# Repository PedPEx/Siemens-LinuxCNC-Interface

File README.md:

# Siemens Sinumerik840C control panel Interface (WIP! - UNTESTED!)
This interface board is designed to be placed on the backside of an [old type](https://mall.industry.siemens.com/mall/de/de/Catalog/Product/6FC5103-0AD03-0AA0) Siemens Sinumerik840C machine control panel in order to be used as user input in LinuxCNC. I reverse engineered a control panel of type M (CNC-Mill - 6FC5103-0AD03-0AA0) for this project. All the IOs of these control panels are accessible through the two 64pin pinheaders. You can get these machine control panels pretty cheap on ebay.

Interface:

Sinumerik840C Machine Control Panel:

## ToDo
- ✅ finished prototype PCB (v0.9.5)
- 🔲 finished prototype PCB (v0.9.6)
- ✅ firmware for STM32L151CC (technically 100% - needs cleanup and timeout detection on LinuxCNC side)
- 🔲 tested intensively with LinuxCNC
- 🔲 example config for LinuxCNC

## Powering
The board needs no seperate supply voltage and is fully powered by the USB Interface. A power distribution switch deactivates the whole interface in case of an overcurrent (set to 1.0 A).

## USB port
Plug in a USB-C cable and use the provided strain relief with the help of a 5mm cable tie. With this USB connection a virtual serial port is used to send the data to the host. More information in the [software](#usagesoftware) details.

## Terminal blocks and general IO
Most of the IO on the three terminal blocks is directly wired into the microcontroller. They can be used for analog inputs or for further expansion in general.

As terminal blocks [Weidmüller 1824460000 - LSF-SMT 3.50/06/90 3.5SN BK TU](https://catalog.weidmueller.com/catalog/Start.do?ObjectID=1824460000) were used - because i had them at hand. But any headers or screw terminals with a 3.5 mm pitch can be used here.

## Usage/Software
This interface board is meant to be used in combination with the software [LinuxCNC_ArduinoConnector](https://github.com/AlexmagToast/LinuxCNC_ArduinoConnector). It does not operate with an Arduino, but with a much more capable [STM32L151C8](https://www.st.com/en/microcontrollers-microprocessors/stm32l151cc.html). The STM32 just emulates a serial port and sends the same signals to the LinuxCNC component like the Arduino would. The L1 series of STM32 was chosen because of its bootloader

## Limitations
Do not use this board for any time critical porpuses!

## Online Preview / BOM
[Detailed schematics preview](https://kicanvas.org/?github=https%3A%2F%2Fgithub.com%2FPedPEx%2FSiemens-LinuxCNC-Interface%2Ftree%2Fmaster%2F1_hardware) (KiCanvas)

[Online BOM](https://htmlpreview.github.io/?https://raw.githubusercontent.com/PedPEx/Siemens-LinuxCNC-Interface/master/1_hardware/bom/webviewer-BOM.html)

[3D Preview](https://github.com/PedPEx/Siemens-LinuxCNC-Interface/blob/master/1_hardware/Siemens-Sinumerik840C-Maschinensteuertafel-Adaptor.stl)

## LinuxCNC config (TODO)
When finished, an example config for LinuxCNC can be found in the [correspondig folder](https://github.com/PedPEx/Siemens-LinuxCNC-Interface/tree/master/2_software_LinuxCNC).

An example of a whole machine fitted with this Interface can be found in my other project [Maho400E-LinuxCNC](https://github.com/PedPEx/Maho400E-LinuxCNC)

## *Note*
The pictures were rendered with the help of Blender and the [pcb2blender](https://github.com/30350n/pcb2blender) plugin and the HTML BOM was created with [InteractiveHtmlBom](https://github.com/openscopeproject/InteractiveHtmlBom).

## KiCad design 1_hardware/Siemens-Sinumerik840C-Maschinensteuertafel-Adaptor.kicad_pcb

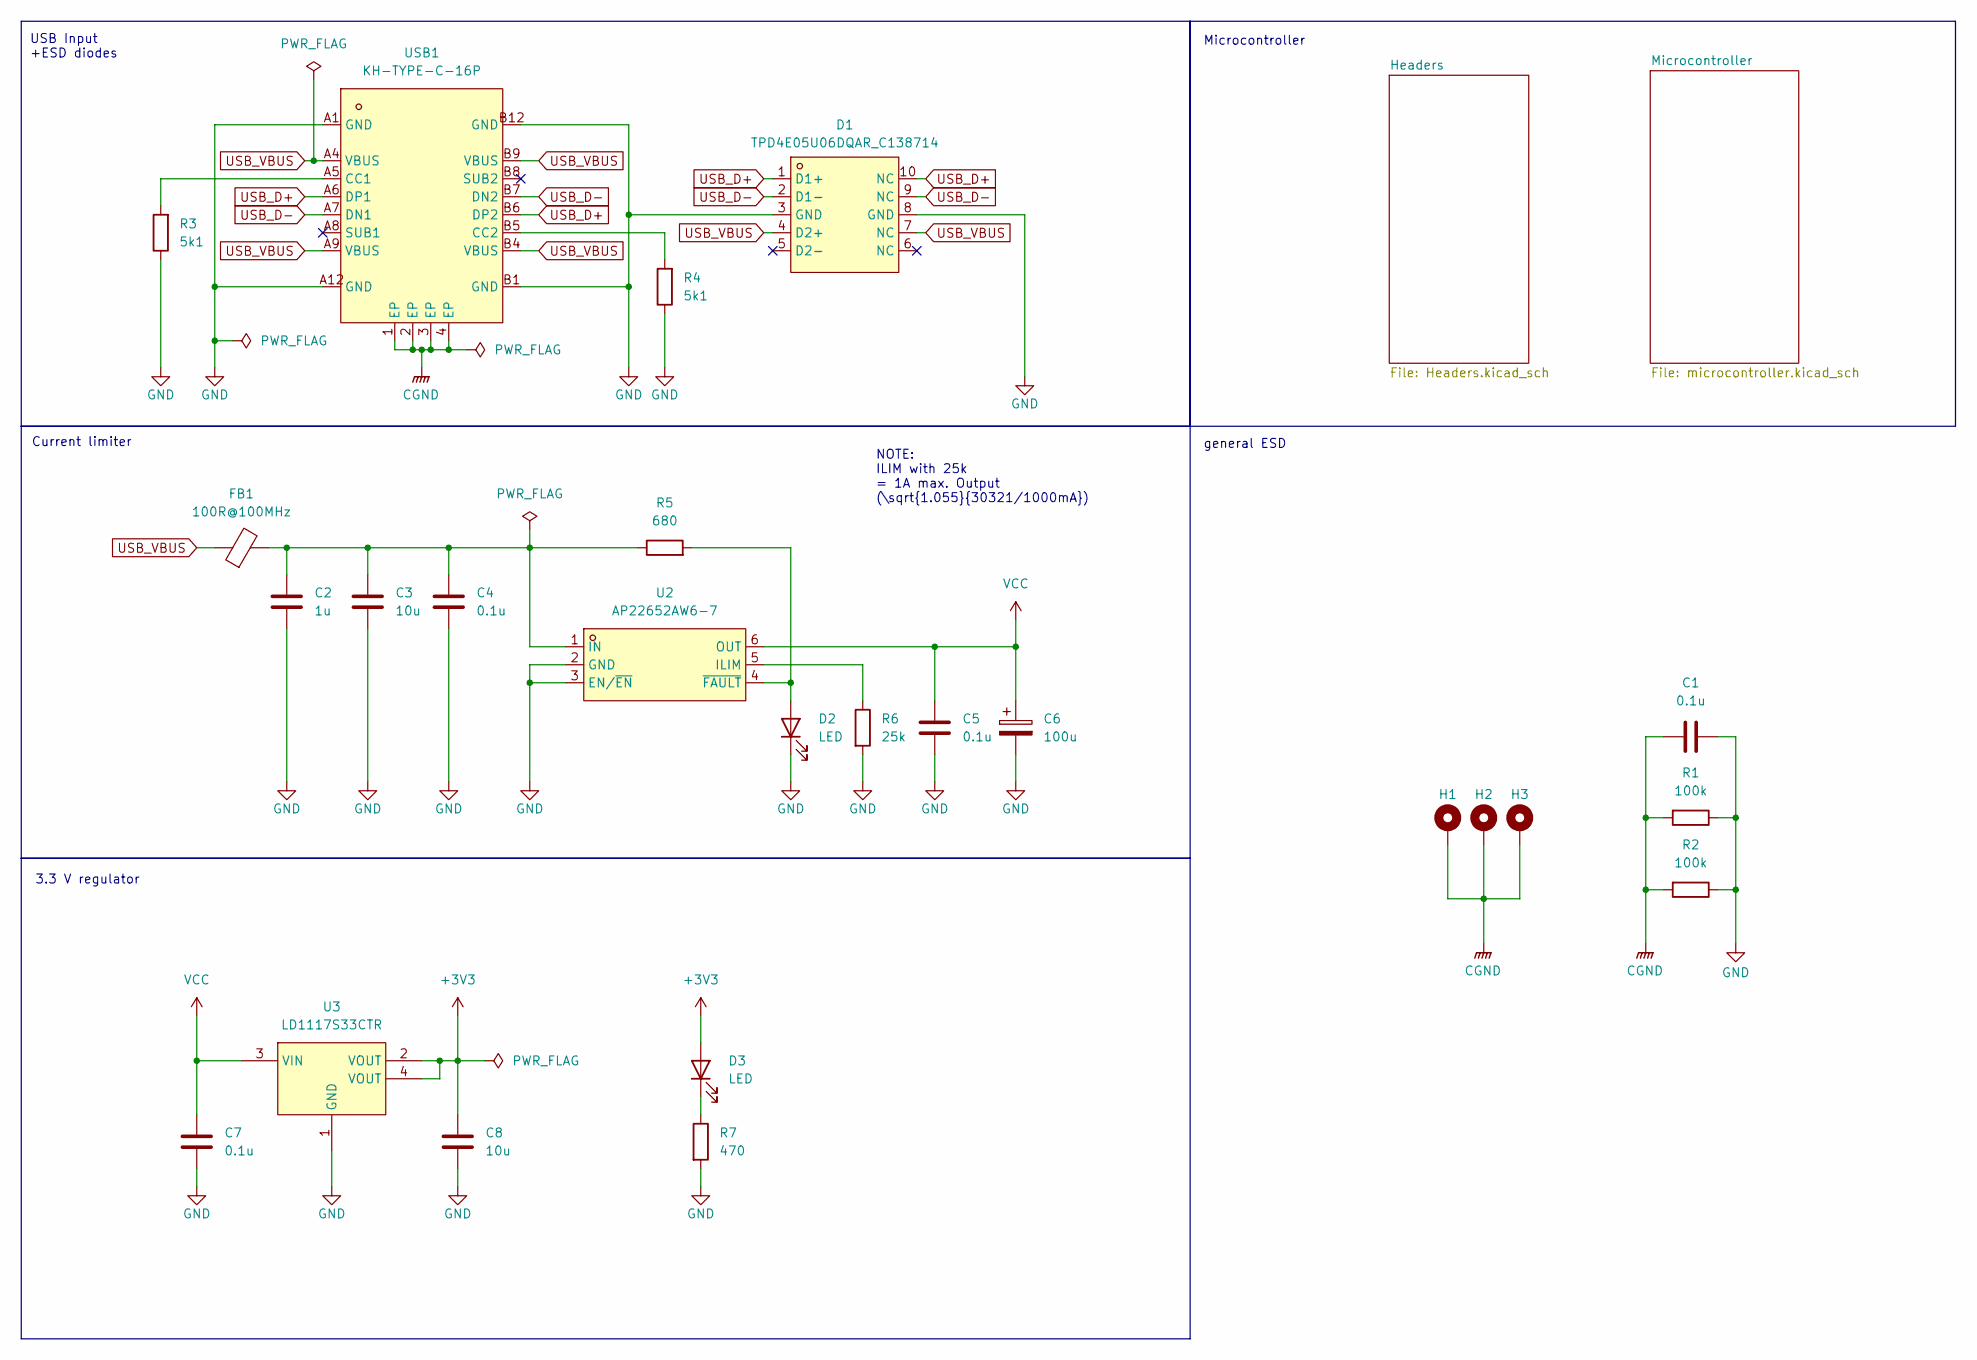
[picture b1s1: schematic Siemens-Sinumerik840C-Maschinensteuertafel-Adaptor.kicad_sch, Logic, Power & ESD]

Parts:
C1: 0.1u; C_2220_5750Metric; LCSC Part C5290327
C2: 1u; C_0603_1608Metric
C3, C8: 10u; C_0603_1608Metric
C4, C5, C7: 0.1u; C_0603_1608Metric
C6: 100u; CP_Elec_5x5.8; LCSC Part C336771
D1: TPD4E05U06DQAR_C138714; USON-10_L2.5-W1.0-P0.50-BL; LCSC Part C138714
D2, D3: LED; LED_0603_1608Metric
FB1: 100R@100MHz; L0603; LCSC Part C107332
H1, H2, H3: MountingHole_Pad_MP; MountingHole_3.2mm_M3_DIN965_Pad
R1, R2: 100k; R_2512_6332Metric; LCSC Part C25717
R3, R4: 5k1; R_0603_1608Metric
R5: 680; R_0603_1608Metric
R6: 25k; R_0603_1608Metric
R7: 470; R_0603_1608Metric
U2: AP22652AW6-7; SOT-23-6_L2.9-W1.6-P0.95-LS2.8-BL; LCSC Part C5329413
U3: LD1117S33CTR; SOT-223-4_L6.5-W3.5-P2.30-LS7.0-BR; LCSC Part C35879
USB1: KH-TYPE-C-16P; USB-C-SMD_KH-TYPE-C-16P; LCSC Part C709357

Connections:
+3V3: C8.2, D3.2 (A), U3.2 (VOUT), U3.4 (VOUT); also elsewhere on the board
CGND: C1.2, H1.1, H2.1, H3.1, R1.2, R2.2, USB1.1 (EP), USB1.2 (EP), USB1.3 (EP), USB1.4 (EP)
GND: C1.1, C2.1, C3.1, C4.1, C5.1, C6.2, C7.1, C8.1, D1.3 (GND), D1.8 (GND), D2.1 (K), R1.1, R2.1, R3.1, R4.1, R6.2, R7.2, U2.2 (GND), U2.3 (EN/~EN), U3.1 (GND), USB1.A1 (GND), USB1.A12 (GND), USB1.B1 (GND), USB1.B12 (GND); also elsewhere on the board
unnamed: D2.2 (A), R5.2, U2.4 (~FAULT)
unnamed: D3.1 (K), R7.1
unnamed: R6.1, U2.5 (ILIM)
unnamed: C2.2, C3.2, C4.2, FB1.2, R5.1, U2.1 (IN)
unnamed: R3.2, USB1.A5 (CC1)
unnamed: R4.2, USB1.B5 (CC2)
USB_D+: D1.1 (D1+), D1.10 (NC), USB1.A6 (DP1), USB1.B6 (DP2); also elsewhere on the board
USB_D-: D1.2 (D1-), D1.9 (NC), USB1.A7 (DN1), USB1.B7 (DN2); also elsewhere on the board
USB_VBUS: D1.4 (D2+), D1.7 (NC), FB1.1, USB1.A4 (VBUS), USB1.A9 (VBUS), USB1.B4 (VBUS), USB1.B9 (VBUS)
VCC: C5.2, C6.1, C7.2, U2.6 (OUT), U3.3 (VIN); also elsewhere on the board

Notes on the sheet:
3.3 V regulator
NOTE: ILIM with 25k = 1A max. Output (\sqrt{1.055}{30321/1000mA})
Microcontroller
Current limiter
general ESD
USB Input +ESD diodes

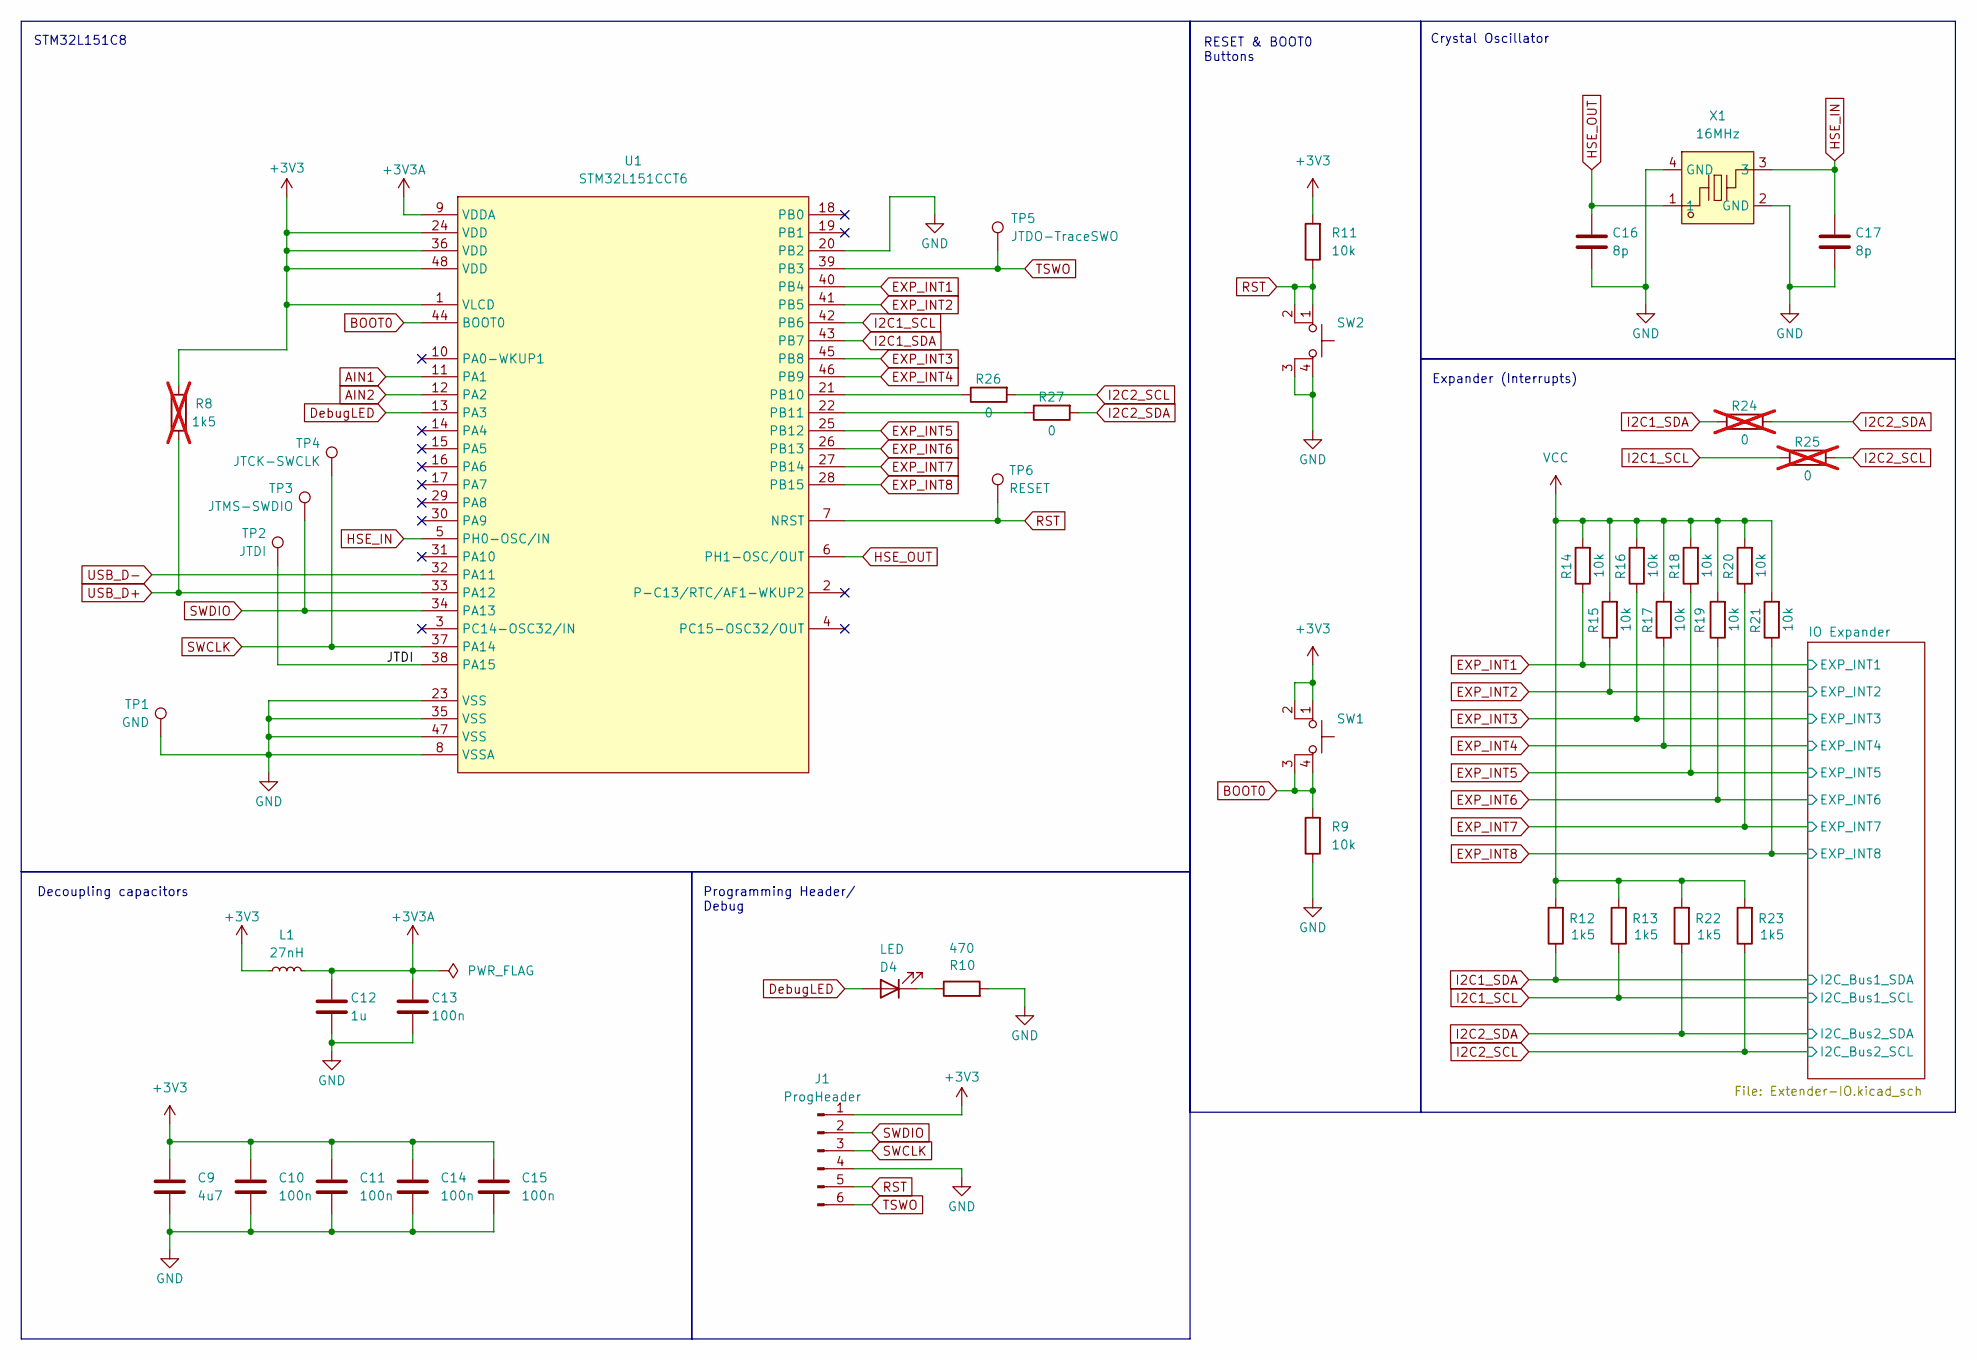
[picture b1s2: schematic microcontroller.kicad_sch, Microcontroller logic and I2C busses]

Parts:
C9: 4u7; C_0603_1608Metric
C10, C11, C13, C14, C15: 100n; C_0603_1608Metric
C12: 1u; C_0603_1608Metric
C16, C17: 8p; C_0603_1608Metric
D4: LED; LED_0603_1608Metric
J1: ProgHeader; HDR-SMD_6P-P2.54-V-M-LS4.8_R2; LCSC Part C2883763
L1: 27nH; L_0603_1608Metric; LCSC Part C12100
R8: 1k5; R_0603_1608Metric; not fitted
R9, R11, R14, R15, R16, R17, R18, R19, R20, R21: 10k; R_0603_1608Metric
R10: 470; R_0603_1608Metric
R12, R13, R22, R23: 1k5; R_0603_1608Metric
R24, R25: 0; R_0603_1608Metric; not fitted
R26, R27: 0; R_0603_1608Metric
SW1, SW2: TS-1187A-B-A-B; SW-SMD_4P-L5.1-W5.1-P3.70-LS6.5-TL-2; LCSC Part C318884
TP1: GND; TestPoint_Pad_D1.0mm
TP2: JTDI; TestPoint_Pad_D1.0mm
TP3: JTMS-SWDIO; TestPoint_Pad_D1.0mm
TP4: JTCK-SWCLK; TestPoint_Pad_D1.0mm
TP5: JTDO-TraceSWO; TestPoint_Pad_D1.0mm
TP6: RESET; TestPoint_Pad_D1.0mm
U1: STM32L151CCT6; LQFP-48_L7.0-W7.0-P0.50-LS9.0-BL; LCSC Part C2149675
X1: 16MHz; CRYSTAL-SMD_4P-L3.2-W2.5-BL_SIT8008BI; LCSC Part C498200

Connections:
+3V3: C9.2, C10.2, C11.2, C14.2, C15.2, J1.1, L1.1, R8.1, R11.2, SW1.1, SW1.2, U1.1 (VLCD), U1.24 (VDD), U1.36 (VDD), U1.48 (VDD); also elsewhere on the board
+3V3A: C12.2, C13.2, L1.2, U1.9 (VDDA)
/Microcontroller/JTDI: TP2.1, U1.38 (PA15)
AIN1: U1.11 (PA1); also elsewhere on the board
AIN2: U1.12 (PA2); also elsewhere on the board
BOOT0: R9.2, SW1.3 (K), SW1.4 (A), U1.44 (BOOT0)
DebugLED: D4.2 (A), U1.13 (PA3)
EXP_INT1: R14.1, U1.40 (PB4); also elsewhere on the board
EXP_INT2: R15.1, U1.41 (PB5); also elsewhere on the board
EXP_INT3: R16.1, U1.45 (PB8); also elsewhere on the board
EXP_INT4: R17.1, U1.46 (PB9); also elsewhere on the board
EXP_INT5: R18.1, U1.25 (PB12); also elsewhere on the board
EXP_INT6: R19.1, U1.26 (PB13); also elsewhere on the board
EXP_INT7: R20.1, U1.27 (PB14); also elsewhere on the board
EXP_INT8: R21.1, U1.28 (PB15); also elsewhere on the board
GND: C9.1, C10.1, C11.1, C12.1, C13.1, C14.1, C15.1, C16.1, C17.1, J1.4, R9.1, R10.2, SW2.3 (K), SW2.4 (A), TP1.1, U1.8 (VSSA), U1.20 (PB2), U1.23 (VSS), U1.35 (VSS), U1.47 (VSS), X1.2 (GND), X1.4 (GND); also elsewhere on the board
HSE_IN: C17.2, U1.5 (PH0-OSC/IN), X1.3
HSE_OUT: C16.2, U1.6 (PH1-OSC/OUT), X1.1
I2C1_SCL: R13.1, R25.1, U1.42 (PB6); also elsewhere on the board
I2C1_SDA: R12.1, R24.1, U1.43 (PB7); also elsewhere on the board
I2C2_SCL: R23.1, R25.2, R26.2; also elsewhere on the board
I2C2_SDA: R22.1, R24.2, R27.2; also elsewhere on the board
unnamed: D4.1 (K), R10.1
unnamed: R26.1, U1.21 (PB10)
unnamed: R27.1, U1.22 (PB11)
RST: J1.5, R11.1, SW2.1, SW2.2, TP6.1, U1.7 (NRST)
SWCLK: J1.3, TP4.1, U1.37 (PA14)
SWDIO: J1.2, TP3.1, U1.34 (PA13)
TSWO: J1.6, TP5.1, U1.39 (PB3)
USB_D+: R8.2, U1.33 (PA12); also elsewhere on the board
USB_D-: U1.32 (PA11); also elsewhere on the board
VCC: R12.2, R13.2, R14.2, R15.2, R16.2, R17.2, R18.2, R19.2, R20.2, R21.2, R22.2, R23.2; also elsewhere on the board

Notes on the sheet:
STM32L151C8
RESET & BOOT0 Buttons
Crystal Oscillator
Decoupling capacitors
Programming Header/ Debug
Expander (Interrupts)

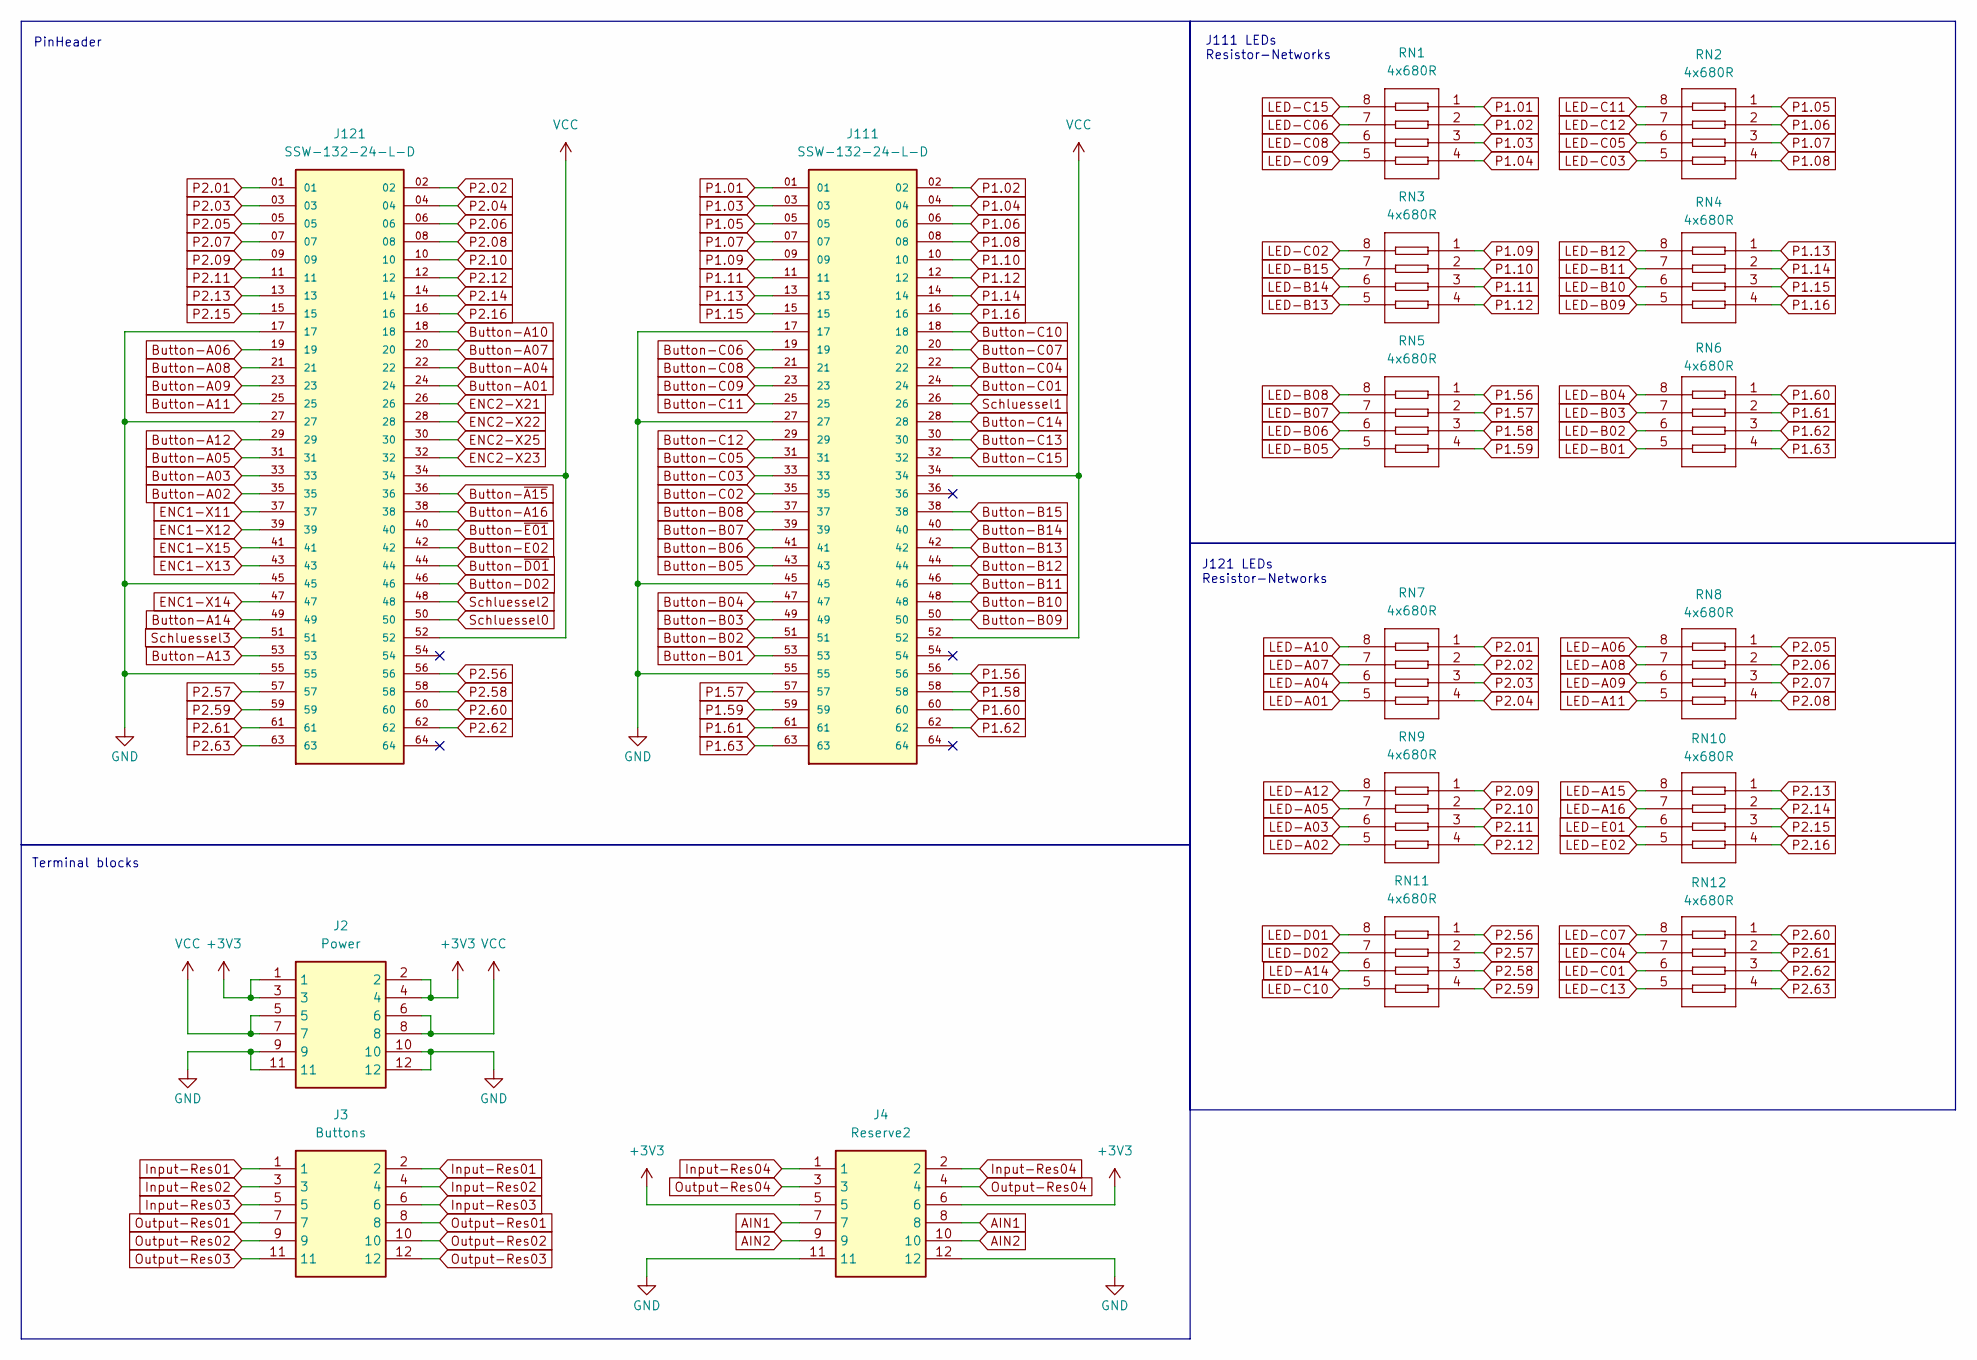
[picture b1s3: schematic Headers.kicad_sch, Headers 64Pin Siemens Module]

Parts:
J2: Power; 1824460000 - LSF-SMT 3.500690 3.5SN BK TU; Manufacturer_Part_Number 1824460000; Mouser Part Number 470-1824460000
J3: Buttons; 1824460000 - LSF-SMT 3.500690 3.5SN BK TU; Manufacturer_Part_Number 1824460000; Mouser Part Number 470-1824460000
J4: Reserve2; 1824460000 - LSF-SMT 3.500690 3.5SN BK TU; Manufacturer_Part_Number 1824460000; Mouser Part Number 470-1824460000
J111, J121: SSW-132-24-L-D; SAMTEC_SSW-132-24-L-D; PARTREV R
RN1, RN2, RN3, RN4, RN5, RN6, RN7, RN8, RN9, RN10, RN11, RN12: 4x680R; RES-ARRAY-SMD_0603-8P-L3.2-W1.6-BL; LCSC Part C12035

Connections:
+3V3: J2.1, J2.2, J2.3, J2.4, J4.5, J4.6; also elsewhere on the board
AIN1: J4.7, J4.8; also elsewhere on the board
AIN2: J4.9, J4.10; also elsewhere on the board
Button-A01: J121.24; also elsewhere on the board
Button-A02: J121.35; also elsewhere on the board
Button-A03: J121.33; also elsewhere on the board
Button-A04: J121.22; also elsewhere on the board
Button-A05: J121.31; also elsewhere on the board
Button-A06: J121.19; also elsewhere on the board
Button-A07: J121.20; also elsewhere on the board
Button-A08: J121.21; also elsewhere on the board
Button-A09: J121.23; also elsewhere on the board
Button-A10: J121.18; also elsewhere on the board
Button-A11: J121.25; also elsewhere on the board
Button-A12: J121.29; also elsewhere on the board
Button-A13: J121.53; also elsewhere on the board
Button-A14: J121.49; also elsewhere on the board
Button-A16: J121.38; also elsewhere on the board
Button-B01: J111.53; also elsewhere on the board
Button-B02: J111.51; also elsewhere on the board
Button-B03: J111.49; also elsewhere on the board
Button-B04: J111.47; also elsewhere on the board
Button-B05: J111.43; also elsewhere on the board
Button-B06: J111.41; also elsewhere on the board
Button-B07: J111.39; also elsewhere on the board
Button-B08: J111.37; also elsewhere on the board
Button-B09: J111.50; also elsewhere on the board
Button-B10: J111.48; also elsewhere on the board
Button-B11: J111.46; also elsewhere on the board
Button-B12: J111.44; also elsewhere on the board
Button-B13: J111.42; also elsewhere on the board
Button-B14: J111.40; also elsewhere on the board
Button-B15: J111.38; also elsewhere on the board
Button-C01: J111.24; also elsewhere on the board
Button-C02: J111.35; also elsewhere on the board
Button-C03: J111.33; also elsewhere on the board
Button-C04: J111.22; also elsewhere on the board
Button-C05: J111.31; also elsewhere on the board
Button-C06: J111.19; also elsewhere on the board
Button-C07: J111.20; also elsewhere on the board
Button-C08: J111.21; also elsewhere on the board
Button-C09: J111.23; also elsewhere on the board
Button-C10: J111.18; also elsewhere on the board
Button-C11: J111.25; also elsewhere on the board
Button-C12: J111.29; also elsewhere on the board
Button-C13: J111.30; also elsewhere on the board
Button-C14: J111.28; also elsewhere on the board
Button-C15: J111.32; also elsewhere on the board
Button-D02: J121.46; also elsewhere on the board
Button-E02: J121.42; also elsewhere on the board
Button-~A15: J121.36; also elsewhere on the board
Button-~D01: J121.44; also elsewhere on the board
Button-~E01: J121.40; also elsewhere on the board
ENC1-X11: J121.37; also elsewhere on the board
ENC1-X12: J121.39; also elsewhere on the board
ENC1-X13: J121.43; also elsewhere on the board
ENC1-X14: J121.47; also elsewhere on the board
ENC1-X15: J121.41; also elsewhere on the board
ENC2-X21: J121.26; also elsewhere on the board
ENC2-X22: J121.28; also elsewhere on the board
ENC2-X23: J121.32; also elsewhere on the board
ENC2-X25: J121.30; also elsewhere on the board
GND: J2.9, J2.10, J2.11, J2.12, J4.11, J4.12, J111.17, J111.27, J111.45, J111.55, J121.17, J121.27, J121.45, J121.55; also elsewhere on the board
Input-Res01: J3.1, J3.2; also elsewhere on the board
Input-Res02: J3.3, J3.4; also elsewhere on the board
Input-Res03: J3.5, J3.6; also elsewhere on the board
Input-Res04: J4.1, J4.2; also elsewhere on the board
LED-A01: RN7.5; also elsewhere on the board
LED-A02: RN9.5; also elsewhere on the board
LED-A03: RN9.6; also elsewhere on the board
LED-A04: RN7.6; also elsewhere on the board
LED-A05: RN9.7; also elsewhere on the board
LED-A06: RN8.8; also elsewhere on the board
LED-A07: RN7.7; also elsewhere on the board
LED-A08: RN8.7; also elsewhere on the board
LED-A09: RN8.6; also elsewhere on the board
LED-A10: RN7.8; also elsewhere on the board
LED-A11: RN8.5; also elsewhere on the board
LED-A12: RN9.8; also elsewhere on the board
LED-A14: RN11.6; also elsewhere on the board
LED-A15: RN10.8; also elsewhere on the board
LED-A16: RN10.7; also elsewhere on the board
LED-B01: RN6.5; also elsewhere on the board
LED-B02: RN6.6; also elsewhere on the board
LED-B03: RN6.7; also elsewhere on the board
LED-B04: RN6.8; also elsewhere on the board
LED-B05: RN5.5; also elsewhere on the board
LED-B06: RN5.6; also elsewhere on the board
LED-B07: RN5.7; also elsewhere on the board
LED-B08: RN5.8; also elsewhere on the board
LED-B09: RN4.5; also elsewhere on the board
LED-B10: RN4.6; also elsewhere on the board
LED-B11: RN4.7; also elsewhere on the board
LED-B12: RN4.8; also elsewhere on the board
LED-B13: RN3.5; also elsewhere on the board
LED-B14: RN3.6; also elsewhere on the board
LED-B15: RN3.7; also elsewhere on the board
LED-C01: RN12.6; also elsewhere on the board
LED-C02: RN3.8; also elsewhere on the board
LED-C03: RN2.5; also elsewhere on the board
LED-C04: RN12.7; also elsewhere on the board
LED-C05: RN2.6; also elsewhere on the board
LED-C06: RN1.7; also elsewhere on the board
LED-C07: RN12.8; also elsewhere on the board
LED-C08: RN1.6; also elsewhere on the board
LED-C09: RN1.5; also elsewhere on the board
LED-C10: RN11.5; also elsewhere on the board
LED-C11: RN2.8; also elsewhere on the board
LED-C12: RN2.7; also elsewhere on the board
LED-C13: RN12.5; also elsewhere on the board
LED-C15: RN1.8; also elsewhere on the board
LED-D01: RN11.8; also elsewhere on the board
LED-D02: RN11.7; also elsewhere on the board
LED-E01: RN10.6; also elsewhere on the board
LED-E02: RN10.5; also elsewhere on the board
Output-Res01: J3.7, J3.8; also elsewhere on the board
Output-Res02: J3.9, J3.10; also elsewhere on the board
Output-Res03: J3.11, J3.12; also elsewhere on the board
Output-Res04: J4.3, J4.4; also elsewhere on the board
P1.01: J111.01, RN1.1
P1.02: J111.02, RN1.2
P1.03: J111.03, RN1.3
P1.04: J111.04, RN1.4
P1.05: J111.05, RN2.1
P1.06: J111.06, RN2.2
P1.07: J111.07, RN2.3
P1.08: J111.08, RN2.4
P1.09: J111.09, RN3.1
P1.10: J111.10, RN3.2
P1.11: J111.11, RN3.3
P1.12: J111.12, RN3.4
P1.13: J111.13, RN4.1
P1.14: J111.14, RN4.2
P1.15: J111.15, RN4.3
P1.16: J111.16, RN4.4
P1.56: J111.56, RN5.1
P1.57: J111.57, RN5.2
P1.58: J111.58, RN5.3
P1.59: J111.59, RN5.4
P1.60: J111.60, RN6.1
P1.61: J111.61, RN6.2
P1.62: J111.62, RN6.3
P1.63: J111.63, RN6.4
P2.01: J121.01, RN7.1
P2.02: J121.02, RN7.2
P2.03: J121.03, RN7.3
P2.04: J121.04, RN7.4
P2.05: J121.05, RN8.1
P2.06: J121.06, RN8.2
P2.07: J121.07, RN8.3
P2.08: J121.08, RN8.4
P2.09: J121.09, RN9.1
P2.10: J121.10, RN9.2
P2.11: J121.11, RN9.3
P2.12: J121.12, RN9.4
P2.13: J121.13, RN10.1
P2.14: J121.14, RN10.2
P2.15: J121.15, RN10.3
P2.16: J121.16, RN10.4
P2.56: J121.56, RN11.1
P2.57: J121.57, RN11.2
P2.58: J121.58, RN11.3
P2.59: J121.59, RN11.4
P2.60: J121.60, RN12.1
P2.61: J121.61, RN12.2
P2.62: J121.62, RN12.3
P2.63: J121.63, RN12.4
Schluessel0: J121.50; also elsewhere on the board
Schluessel1: J111.26; also elsewhere on the board
Schluessel2: J121.48; also elsewhere on the board
Schluessel3: J121.51; also elsewhere on the board
VCC: J2.5, J2.6, J2.7, J2.8, J111.34, J111.52, J121.34, J121.52; also elsewhere on the board

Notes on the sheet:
Terminal blocks
J121 LEDs Resistor-Networks
PinHeader
J111 LEDs Resistor-Networks

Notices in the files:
1_hardware/Siemens-Sinumerik840C-Maschinensteuertafel-Adaptor.kicad_pcb:
©PedPEx
